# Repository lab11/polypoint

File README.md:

PolyPoint
=========

PolyPoint is a system for using ultra-wideband RF time-of-flight ranging to perform indoor localization.
It incorporates the DecaWave DW1000 for UWB packet transmission and timestamping
into a solder-on module that provides node-to-node ranges over an I2C interface.

Name
----

The name PolyPoint comes from the use of many polygons and shapes in the prototype design and the
desire to pinpoint where users are with the system.

Git Clone
---------

When cloning this repository, be absolutely sure to do

    git clone --recursive https://github.com/lab11/polypoint.git
    
so that you get the submodules as well. All of the supporting
libraries and build tools are in submodules for the various
hardware platforms used in this project.

Hardware
--------

The PolyPoint system is composed of several hardware pieces. At the core is the
TriPoint module which is a 1.25" on a side triangle that encompasses all of the
core ranging hardware and software. TriPoint has castellated edges and can be
soldered on to a carrier board, effectively as a ranging IC. TriTag is one such
carrier board designed to be the tag in the ranging system. It includes the
UWB antennas and a Bluetooth Low Energy radio plus a battery charging circuit.
TriTag is able to provide ranges to a mobile phone application.

### TriPoint

TriPoint includes the following components:

- DecaWave DW1000 UWB radio
- STM32F031G6U6 MCU
- RF switch

The MCU contains all the necessary code to run the DW1000 and the ranging
protocol.

### TriTag

TriTag includes:

- The TriPoint module
- 3 UWB antennas
- nRF51822 BLE radio
- 3.3 V LDO
- Li-ion battery charger

TriTag is designed to be the tag to be localized in the system and connected
to a smartphone.

### TriDev

TriDev is a breakout and testing board for the TriPoint module.
It contains the same BLE hardware as TriTag, but also adds an FTDI
chip for issuing I2C commands over USB.

Software
--------

PolyPoint contains many software layers that run at various levels of
the system.

#### TriPoint

The core firmware that makes the drop-in TriPoint module work
includes all of the logic to implement two way ToF ranging
on top of the DecaWave DW1000 UWB radio. The firmware architecture
supports multiple "applications", or ranging algorithms, that can
be selected at runtime.

#### TriTag

The TriTag code implements a BLE application
that uses the TriPoint module as an I2C device and prov
a BLE service. It puts the TriTag hardware into TAG mode
and provides ranges over a BLE characteristic. 

#### Phone and BLE

The tools in the `/phone` directory interact with TriTag and read data
across the BLE interface.

----

## Academic Publications

The PolyPoint project has led to two academic publications, and an invited talk at HotWireless'16.
If you are interested in the theory behind the ranging protocol, please check out our publications:

 - **[SurePoint: Exploiting Ultra Wideband Flooding and Diversity to Provide Robust, Scalable, High-Fidelity Indoor Localization.](http://lab11.eecs.berkeley.edu/content/pubs/kempke16surepoint.pdf)** Benjamin Kempke, Pat Pannuto, Bradford Campbell, and Prabal Dutta. Proceedings of the 14th ACM Conference on Embedded Networked Sensor Systems (SenSys’16).
 - **[PolyPoint: Guiding Indoor Quadrotors with Ultra-Wideband Localization.](http://lab11.eecs.berkeley.edu/content/pubs/kempke15polypoint.pdf)** Benjamin Kempke, Pat Pannuto, and Prabal Dutta. 2015 ACM Workshop on Hot Topics in Wireless (HotWireless’15).
 
If you use PolyPoint or its derivatives, please use the following citation:

```bibtex
@inproceedings{kempke16surepoint,
	title = {{SurePoint}: Exploiting Ultra Wideband Flooding and Diversity to Provide Robust, Scalable, High-Fidelity Indoor Localization},
	booktitle = {Proceedings of the 14th ACM Conference on Embedded Networked Sensor Systems},
	series = {SenSys'16},
	year = {2016},
	month = {11},
	location = {Stanford, CA, USA},
	conference-url = {http://sensys.acm.org/2016/},
	author = {Kempke, Benjamin and Pannuto, Pat and Campbell, Bradford and Dutta, Prabal},
}
```

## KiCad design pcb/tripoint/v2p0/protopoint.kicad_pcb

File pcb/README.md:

PolyPoint Hardware
==================

The PolyPoint system consists of several PCBs centered around TriPoint,
the core UWB ranging module.

1. **TriPoint**: Triangular module which contains all necessary hardware
for using the DecaWave DW1000. It has castellated headers so it can be
soldered onto a carrier board to add indoor localization functionality
to any device.

2. **TriTag**: Portable carrier board designed to be used as an indoor
localization tag. Has TriPoint on one side and a BLE radio on the other.

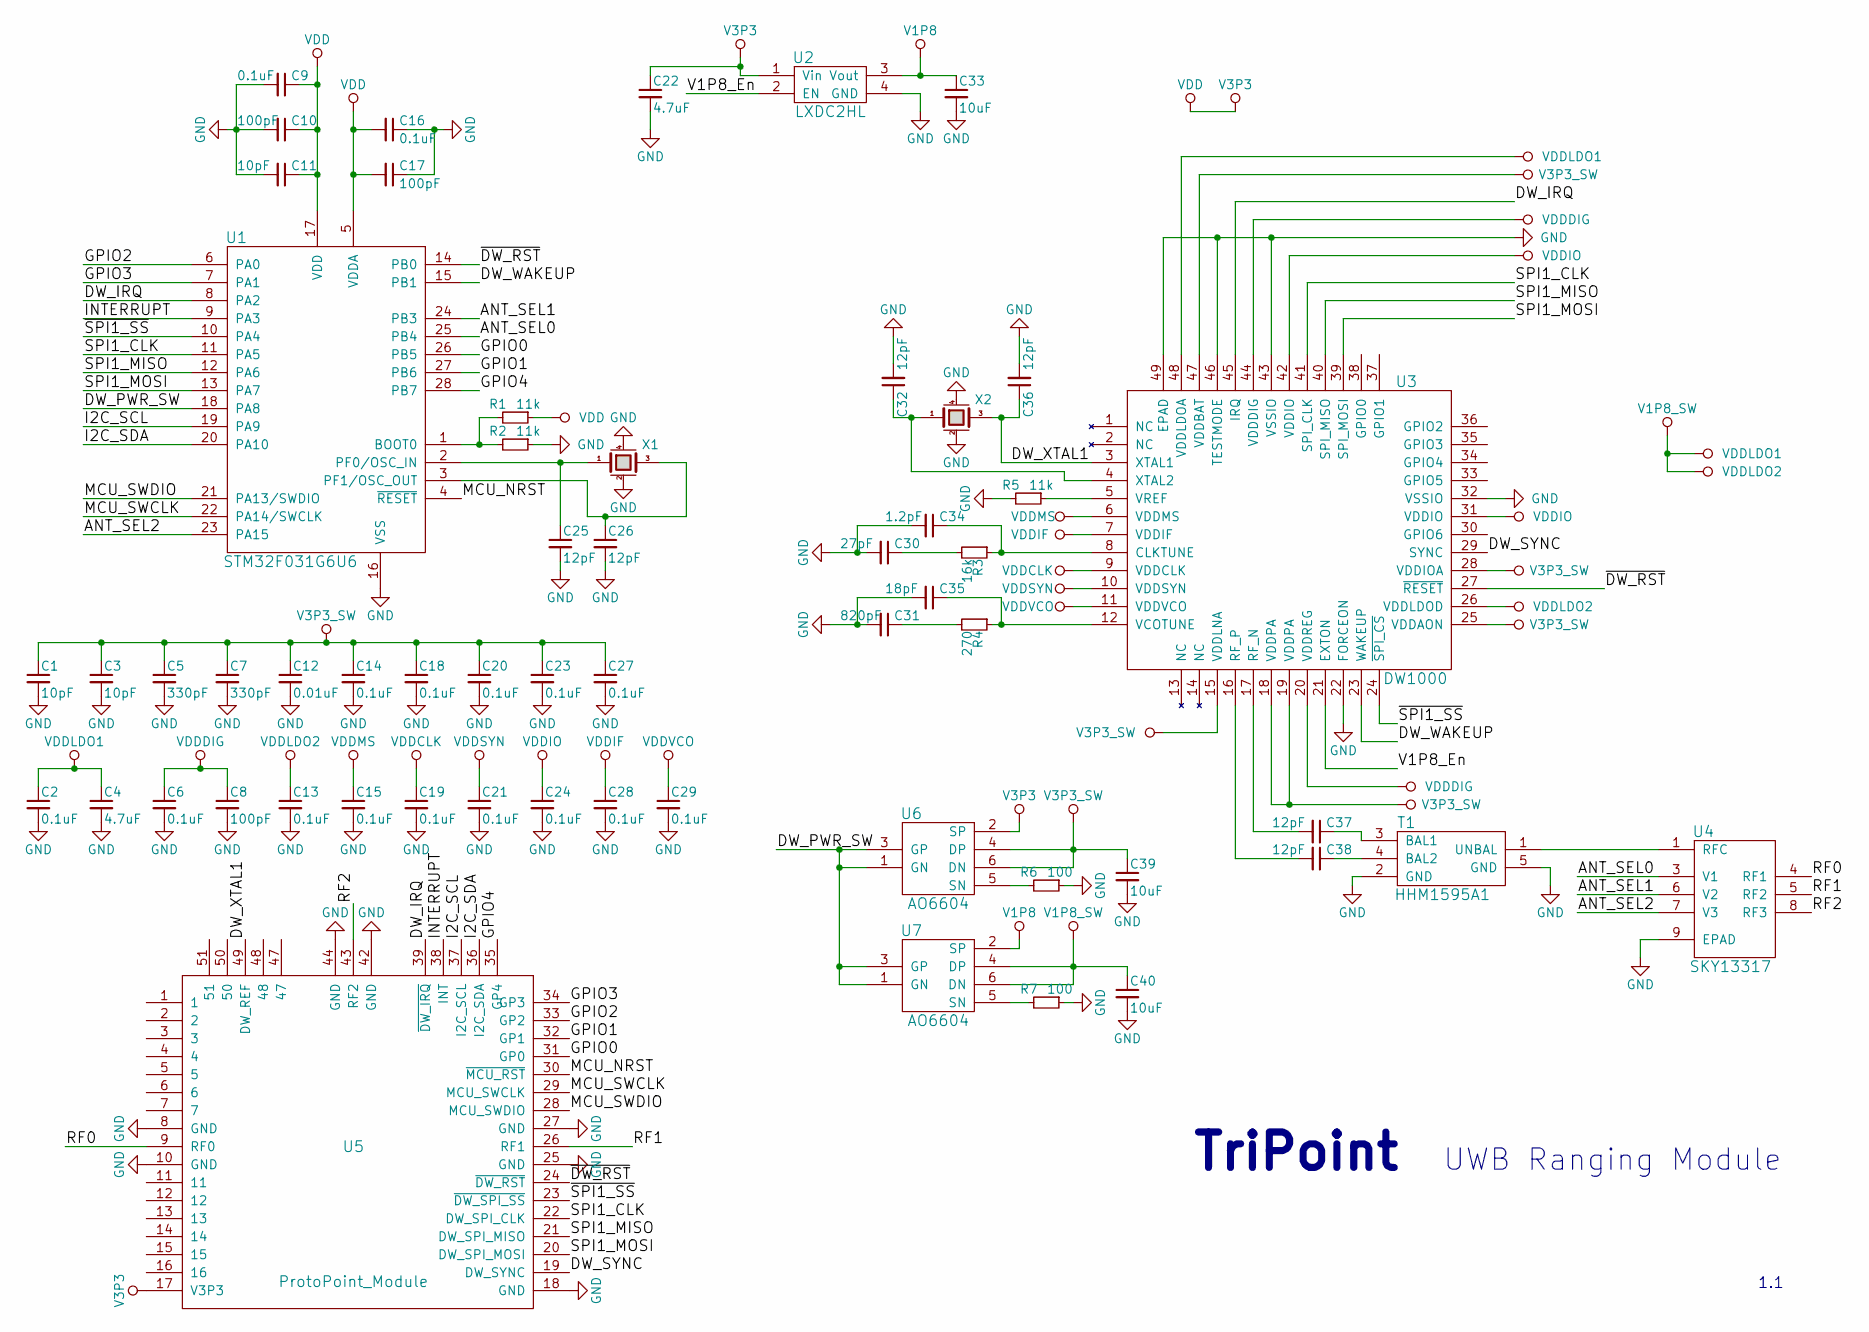
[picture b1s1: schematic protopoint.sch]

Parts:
C1, C3, C11: 10pF; C_0201; ManPartNo GRM0335C1E100JA01D
C2, C6, C9, C13, C14, C15, C16, C18, C19, C20, C21, C23, C24, C27, C28, C29: 0.1uF; C_0201; ManPartNo GRM033R61A104KE15D
C4, C22: 4.7uF; C_0603; ManPartNo GRM188F51A475ZE20D
C5, C7: 330pF; C_0201; ManPartNo GRM033R71E331KA01D
C8, C10, C17: 100pF; C_0201; ManPartNo GRM0335C1E101JA01D
C12: 0.01uF; C_0201; ManPartNo GRM033R71A103KA01D
C25, C26, C32, C36: 12pF; C_0201; ManPartNo GRM0335C1E120JA01D
C30: 27pF; C_0201; ManPartNo GRM0335C1E270JA01D
C31: 820pF; C_0201; ManPartNo GRM033R71E821KA01D
C33, C39, C40: 10uF; C_0603; ManPartNo GRM188R61C106MA73D
C34: 1.2pF; C_0201; ManPartNo GRM0335C1H1R2CA01D
C35: 18pF; C_0201; ManPartNo GRM0335C1H180JA01D
C37, C38: 12pF; C_0402; ManPartNo GRM1555C1H120JA01D
R1, R2, R5: 11k; R_0201; ManPartNo ERJ-1GEF1102C
R3: 16k; R_0201; ManPartNo ERJ-1GEF1602C
R4: 270; R_0201; ManPartNo ERJ-1GEF2700C
R6, R7: 100; R_0201; ManPartNo ERJ-1GEF1102C
T1: HHM1595A1; ManPartNo HHM1595A1
U1: STM32F031G6U6; UFQFPN-28; ManPartNo STM32F031G6U6
U2: LXDC2HL; ManPartNo LXDC2HL18A-052
U3: DW1000; QFN-48-EP-6x6mm; ManPartNo DW1000-I-TR13
U4: SKY13317; MLPQ-UT-8-1.5X1.5mm; ManPartNo SKY13317-373LF
U5: ProtoPoint_Module; ProtoPoint_Module_Castellated
U6, U7: AO6604; TSOP-6
X1: 38.4M; FA-128; ManPartNo FA-20H 38.4000MF10Z-AS3
X2: 16M; FA-128; ManPartNo FA-20H 16.0000MF10Z-AJ3

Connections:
/ANT_SEL0: U1.25 (PB4), U4.3 (V1)
/ANT_SEL1: U1.24 (PB3), U4.6 (V2)
/ANT_SEL2: U1.23 (PA15), U4.7 (V3)
/DW_IRQ: U1.8 (PA2), U3.45 (IRQ), U5.39 (~DW_IRQ)
/DW_PWR_SW: U1.18 (PA8), U6.1 (GN), U6.3 (GP), U7.1 (GN), U7.3 (GP)
/DW_SYNC: U3.29 (SYNC), U5.19 (DW_SYNC)
/DW_WAKEUP: U1.15 (PB1), U3.23 (WAKEUP)
/DW_XTAL1: C36.1, U3.3 (XTAL1), U5.49 (DW_REF), X2.3
/GPIO0: U1.26 (PB5), U5.31 (GP0)
/GPIO1: U1.27 (PB6), U5.32 (GP1)
/GPIO2: U1.6 (PA0), U5.33 (GP2)
/GPIO3: U1.7 (PA1), U5.34 (GP3)
/GPIO4: U1.28 (PB7), U5.35 (GP4)
/I2C_SCL: U1.19 (PA9), U5.37 (I2C_SCL)
/I2C_SDA: U1.20 (PA10), U5.36 (I2C_SDA)
/INTERRUPT: U1.9 (PA3), U5.38 (INT)
/MCU_NRST: U1.4 (~RESET), U5.30 (~MCU_RST)
/MCU_SWCLK: U1.22 (PA14/SWCLK), U5.29 (MCU_SWCLK)
/MCU_SWDIO: U1.21 (PA13/SWDIO), U5.28 (MCU_SWDIO)
/RF0: U4.4 (RF1), U5.9 (RF0)
/RF1: U4.5 (RF2), U5.26 (RF1)
/RF2: U4.8 (RF3), U5.43 (RF2)
/SPI1_CLK: U1.11 (PA5), U3.41 (SPI_CLK), U5.22 (DW_SPI_CLK)
/SPI1_MISO: U1.12 (PA6), U3.40 (SPI_MISO), U5.21 (DW_SPI_MISO)
/SPI1_MOSI: U1.13 (PA7), U3.39 (SPI_MOSI), U5.20 (DW_SPI_MOSI)
/V1P8_En: U2.2 (EN), U3.21 (EXTON)
/~DW_RST: U1.14 (PB0), U3.27 (~RESET), U5.24 (~DW_RST)
/~SPI1_SS: U1.10 (PA4), U3.24 (~SPI_CS), U5.23 (~DW_SPI_SS)
GND: C1.2, C2.2, C3.2, C4.2, C5.2, C6.2, C7.2, C8.2, C9.2, C10.2, C11.2, C12.2, C13.2, C14.2, C15.2, C16.1, C17.1, C18.2, C19.2, C20.2, C21.2, C22.2, C23.2, C24.2, C25.2, C26.2, C27.2, C28.2, C29.2, C30.2, C31.2, C32.2, C33.2, C34.2, C35.2, C36.2, C39.2, C40.2, R2.1, R5.2, R6.1, R7.1, T1.2 (GND), T1.5 (GND), U1.16 (VSS), U2.4 (GND), U3.22 (FORCEON), U3.32 (VSSIO), U3.43 (VSSIO), U3.46 (TESTMODE), U3.49 (EPAD), U4.9 (EPAD), U5.8 (GND), U5.10 (GND), U5.18 (GND), U5.25 (GND), U5.27 (GND), U5.42 (GND), U5.44 (GND), X1.2 (case), X1.4, X2.2 (case), X2.4
unnamed: C25.1, U1.2 (PF0/OSC_IN), X1.1
unnamed: C26.1, U1.3 (PF1/OSC_OUT), X1.3
unnamed: C30.1, R3.2
unnamed: C31.1, R4.2
unnamed: C32.1, U3.4 (XTAL2), X2.1
unnamed: C34.1, R3.1, U3.8 (CLKTUNE)
unnamed: C35.1, R4.1, U3.12 (VCOTUNE)
unnamed: C37.1, T1.3 (BAL1)
unnamed: C37.2, U3.17 (RF_N)
unnamed: C38.1, T1.4 (BAL2)
unnamed: C38.2, U3.16 (RF_P)
unnamed: R1.2, R2.2, U1.1 (BOOT0)
unnamed: R5.1, U3.5 (VREF)
unnamed: R6.2, U6.5 (SN)
unnamed: R7.2, U7.5 (SN)
unnamed: T1.1 (UNBAL), U4.1 (RFC)
V1P8: C33.1, U2.3 (Vout), U7.2 (SP)
V1P8_SW: C2.1, C4.1, C13.1, C40.1, U3.26 (VDDLDOD), U3.48 (VDDLDOA), U7.4 (DP), U7.6 (DN)
V3P3: C9.1, C10.1, C11.1, C16.2, C17.2, C22.1, R1.1, U1.5 (VDDA), U1.17 (VDD), U2.1 (Vin), U5.17 (V3P3), U6.2 (SP)
V3P3_SW: C1.1, C3.1, C5.1, C7.1, C12.1, C14.1, C18.1, C20.1, C23.1, C27.1, C39.1, U3.15 (VDDLNA), U3.18 (VDDPA), U3.19 (VDDPA), U3.25 (VDDAON), U3.28 (VDDIOA), U3.47 (VDDBAT), U6.4 (DP), U6.6 (DN)
VDDCLK: C19.1, U3.9 (VDDCLK)
VDDDIG: C6.1, C8.1, U3.20 (VDDREG), U3.44 (VDDDIG)
VDDIF: C28.1, U3.7 (VDDIF)
VDDIO: C24.1, U3.31 (VDDIO), U3.42 (VDDIO)
VDDMS: C15.1, U3.6 (VDDMS)
VDDSYN: C21.1, U3.10 (VDDSYN)
VDDVCO: C29.1, U3.11 (VDDVCO)

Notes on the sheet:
TriPoint
1.1
UWB Ranging Module

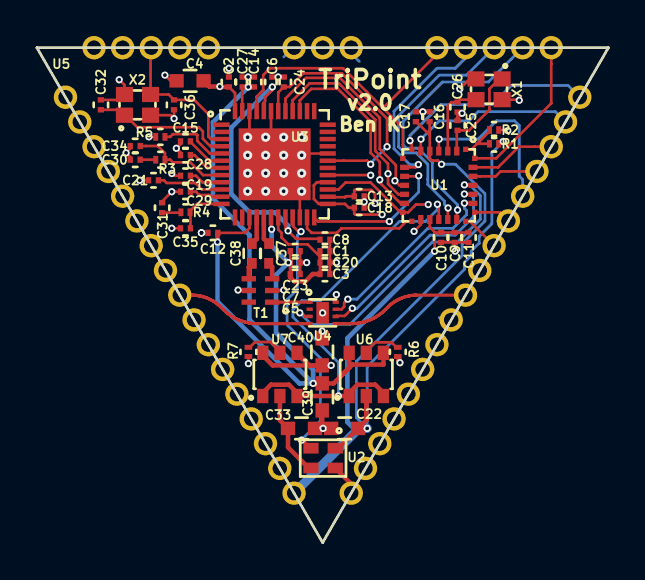
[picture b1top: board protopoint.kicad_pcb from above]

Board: 4 copper layers, 31.8 x 27.5 mm, 57 parts (0 on the bottom side), 56 nets.

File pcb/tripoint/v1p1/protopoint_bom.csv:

Reference, Quantity, Value, Footprint, Datasheet, ManPartNo, DistPartNo
C1 C11 C3 ,3,10pF,Capacitors_SMD:C_0201,,GRM0335C1E100JA01D,490-8607-1-ND
C12 ,1,0.01uF,Capacitors_SMD:C_0201,,GRM033R71A103KA01D,490-3194-1-ND
C13 C14 C15 C16 C18 C19 C2 C20 C21 C23 C24 C27 C28 C29 C6 C9 ,16,0.1uF,Capacitors_SMD:C_0201,,GRM033R61A104KE15D,490-5881-1-ND
C10 C17 C8 ,3,100pF,Capacitors_SMD:C_0201,,GRM0335C1E101JA01D,490-3160-1-ND
C22 C4 ,2,4.7uF,Capacitors_SMD:C_0603,,GRM188F51A475ZE20D,490-3302-1-ND
C25 C26 C32 C36 ,4,12pF,Capacitors_SMD:C_0201,,GRM0335C1E120JA01D,490-3144-1-ND
C30 ,1,27pF,Capacitors_SMD:C_0201,,GRM0335C1E270JA01D,490-3150-1-ND
C31 ,1,820pF,Capacitors_SMD:C_0201,,GRM033R71E821KA01D,490-3183-1-ND
C33 ,1,10uF,Capacitors_SMD:C_0603,,GRM188R61C106MA73D,490-7201-1-ND
C34 ,1,1.2pF,Capacitors_SMD:C_0201,,GRM0335C1H1R2CA01D,490-6119-1-ND
C35 ,1,18pF,Capacitors_SMD:C_0201,,GRM0335C1H180JA01D,490-6117-1-ND
C37 C38 ,2,12pF,Capacitors_SMD:C_0402,,GRM1555C1H120JA01D,490-5924-1-ND
C5 C7 ,2,330pF,Capacitors_SMD:C_0201,,GRM033R71E331KA01D,490-3178-1-ND
R3 ,1,16k,Resistors_SMD:R_0201,,ERJ-1GEF1602C,P16.0KABCT-ND
R4 ,1,270,Resistors_SMD:R_0201,,ERJ-1GEF2700C,P270ABCT-ND
R1 R2 R5 ,3,11k,Resistors_SMD:R_0201,,ERJ-1GEF1102C,P11.0KABCT-ND
T1 ,1,HHM1595A1,polypoint:HHM1595A1,,HHM1595A1,445-3387-1-ND
U1 ,1,STM32F031G6U6,polypoint:UFQFPN-28,,STM32F031G6U6,497-13620-ND
U2 ,1,LXDC2HL,polypoint:LXDC2HL,,LXDC2HL18A-052,490-5791-1-ND
U3 ,1,DW1000,polypoint:QFN-48-EP-6x6mm,,DW1000-I-TR13,1479-1001-1-ND
U4 ,1,SKY13317,polypoint:MLPQ-UT-8-1.5X1.5mm,,SKY13317-373LF,863-1056-1-ND
U5 ,1,ProtoPoint_Module,polypoint:ProtoPoint_Module_Castellated,
X1 ,1,38.4M,polypoint:FA-128,,FA-20H 38.4000MF10Z-AS3,SER3631CT-ND
X2 ,1,16M,polypoint:FA-128,,FA-20H 16.0000MF10Z-AJ3,SER3913CT-ND

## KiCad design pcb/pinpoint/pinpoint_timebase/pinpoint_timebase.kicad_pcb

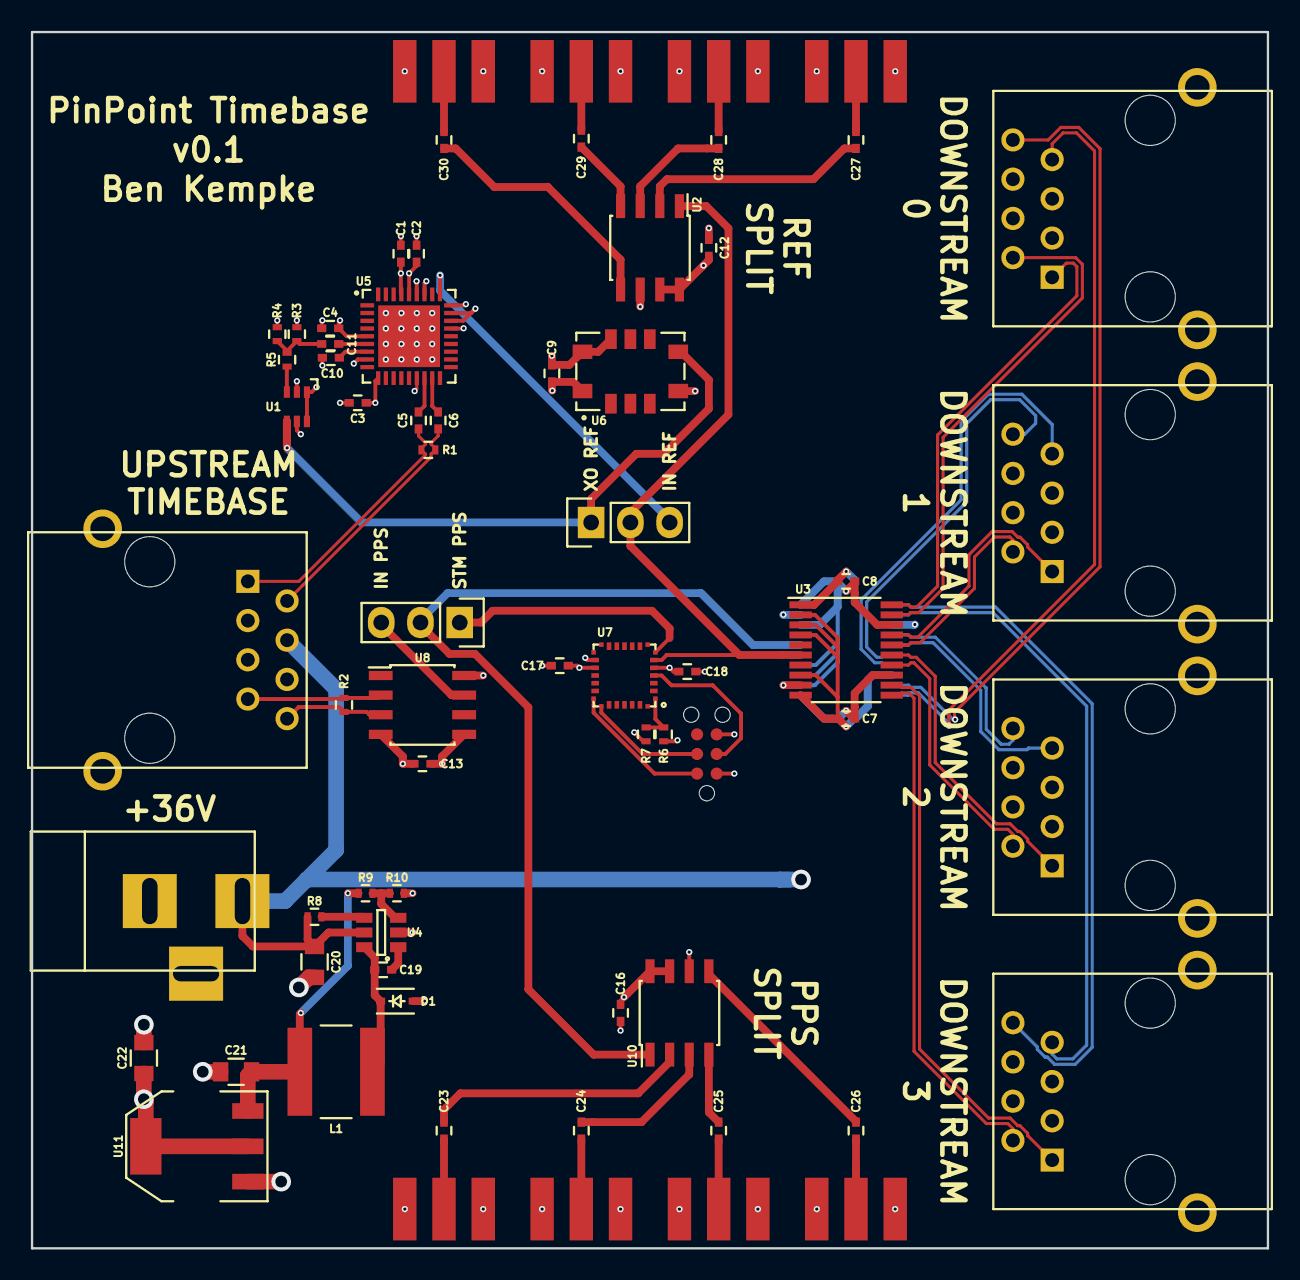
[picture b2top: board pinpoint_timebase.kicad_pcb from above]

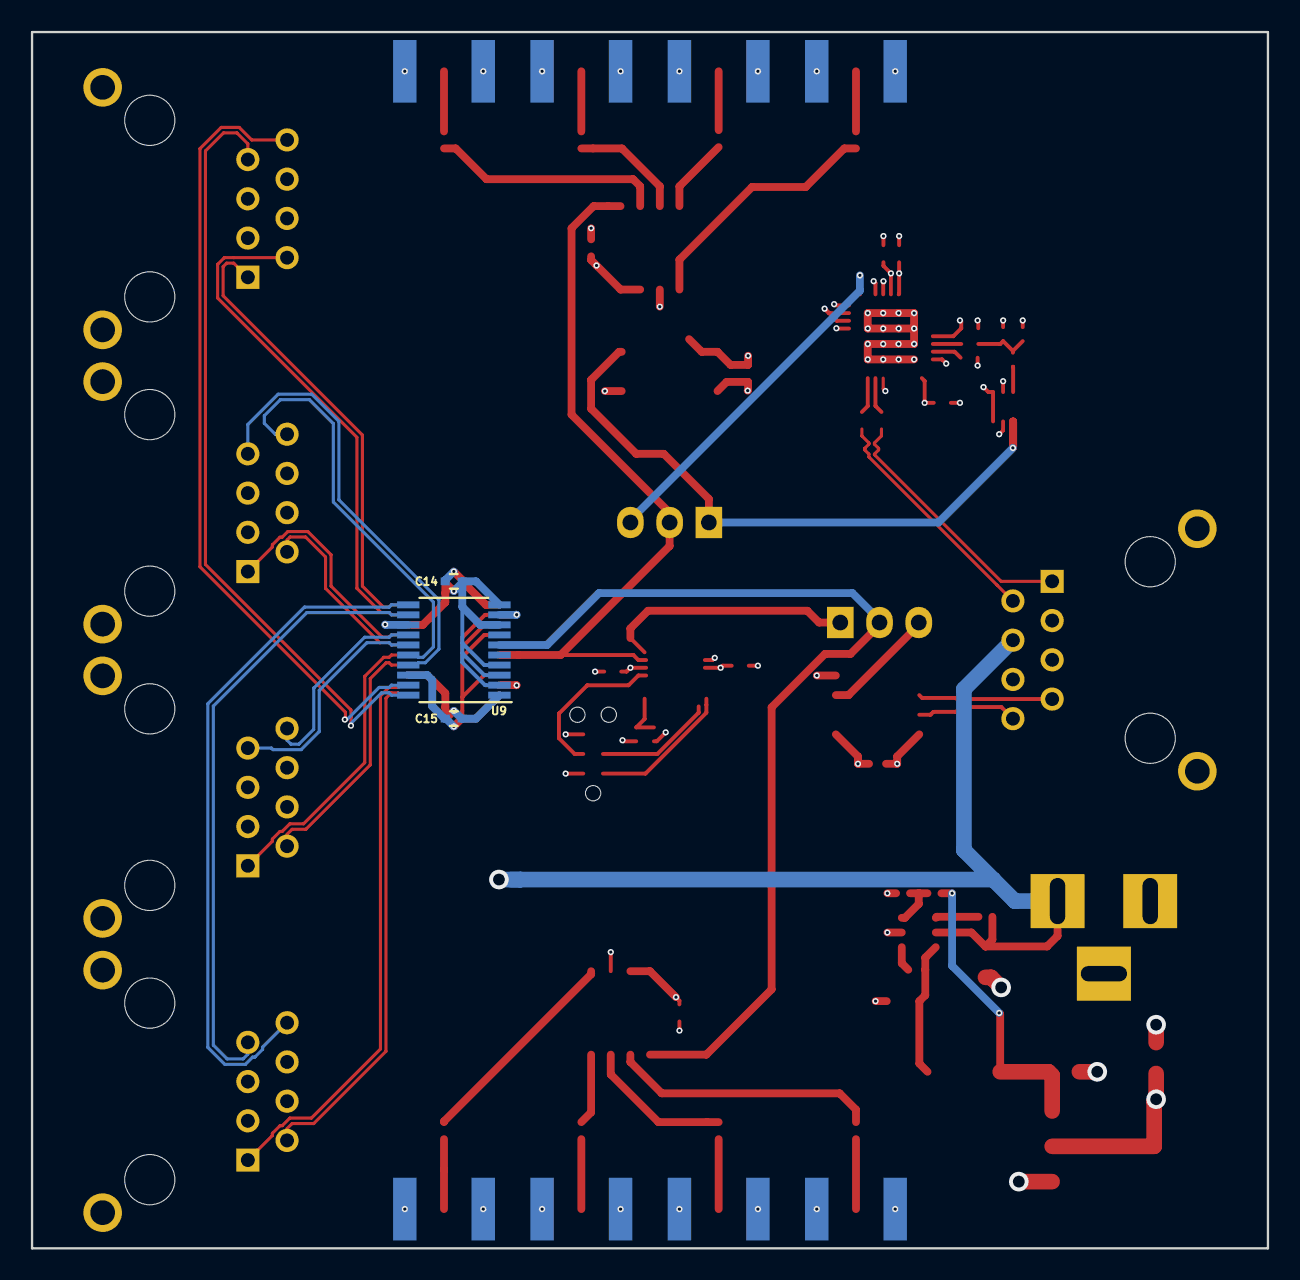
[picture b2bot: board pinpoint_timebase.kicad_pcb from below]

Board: 4 copper layers, 80.0 x 78.7 mm, 70 parts (3 on the bottom side), 60 nets.

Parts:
C1, C2, C3, C4, C5, C6, C7, C8, C9, C10, C11, C12, C13, C14, C15, C16, C17, C18, C19, C23, C24, C25, C26, C27, C28, C29, C30: 0.1uF; C_0402
C20: 4.7uF; C_0805
C21, C22: 10uF; C_0805
CON1: BARREL_JACK
D1: D_Schottky; SOD-323
J1, J2, J3, J4, J5: RJ45; RJ45_8
J6: TC2030-JLINK-NL; TC2030
L1: 22uH; NR6045
P1, P6: CONN_01X03; Pin_Header_Straight_1x03
P2, P3, P4, P5, P8, P9, P10: SMA; SMA_EDGE
R1, R2, R6, R7: R_Small; R_0402
R3, R4: 150; R_0402
R5: 130; R_0402
R8: 4.7K; R_0402
R9: 49.9K; R_0402
R10: 9.53K; R_0402
U1: SN74AVC1T45; SC-70-6
U2, U10: 551S; SOIC-8_3.9x4.9mm_Pitch1.27mm
U3, U9: ICS8545; TSSOP-20_4.4x6.5mm_Pitch0.65mm
U4: AOZ1282CI; SOT-23-6
U5: SI5317; QFN-36_1EP_6x6mm
U6: 7N-XX.XXXMBP-T; 7N-xx.xxxMBP-T
U7: STM32F031G4U6; UFQFPN-28
U8: 830S21; SOIC-8_3.9x4.9mm_Pitch1.27mm
U11: NCP1117; SOT-223
eP7: SMA; SMA_EDGE

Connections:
/CLK0+: J3.1, U3.20
/CLK0-: J3.2, U3.19
/CLK1+: J4.1, U3.17
/CLK1-: J4.2, U3.16
/CLK2+: J1.1, U3.15
/CLK2-: J1.2, U3.14
/CLK3+: J5.1, U3.12
/CLK3-: J5.2, U3.11
/IN_PPS+: J2.7, R2.1, U8.2
/IN_PPS-: J2.8, R2.2, U8.3
/IN_REF+: C5.2, J2.1, R1.1
/IN_REF-: C6.2, J2.2, R1.2
/PPS0+: J3.7, U9.20
/PPS0-: J3.8, U9.19
/PPS1+: J4.7, U9.17
/PPS1-: J4.8, U9.16
/PPS2+: J1.7, U9.15
/PPS2-: J1.8, U9.14
/PPS3+: J5.7, U9.12
/PPS3-: J5.8, U9.11
/REFTMP+: C5.1, U5.16
/REFTMP-: C6.1, U5.17
/SYS_CLK: P1.2, U2.1, U3.6, U7.6
GND: C1.2, C2.1, C3.2, C4.1, C7.2, C8.1, C9.2, C10.1, C12.2, C13.2, C14.2, C15.1, C16.2, C17.2, C18.1, C20.2, C21.2, C22.2, CON1.2, CON1.3, D1.2, J1.5, J1.9, J2.5, J2.9, J3.5, J3.9, J4.5, J4.9, J5.5, J5.9, J6.5, P2.2, P3.2, P4.2, P5.2, P8.2, P9.2, P10.2, R4.1, R7.2, R10.2, U1.2, U1.5, U2.6, U3.1, U3.9, U3.13, U4.2, U5.8, U5.15, U5.24, U5.27, U5.30, U5.31, U5.37, U6.4, U6.10, U7.16, U8.5, U9.1, U9.9, U9.13, U10.6, U11.1, eP7.2
unnamed: C10.2, U5.7
unnamed: C11.1, R3.1, R4.2, R5.2
unnamed: C11.2, U5.6
unnamed: C19.1, D1.1, L1.1, U4.6
unnamed: C19.2, U4.1
unnamed: C21.1, L1.2, R9.1, U11.3
unnamed: C23.1, U10.2
unnamed: C23.2, eP7.1
unnamed: C24.1, U10.3
unnamed: C24.2, P8.1
unnamed: C25.1, U10.4
unnamed: C25.2, P9.1
unnamed: C26.1, U10.5
unnamed: C26.2, P10.1
unnamed: C27.1, U2.2
unnamed: C27.2, P2.1
unnamed: C28.1, U2.3
unnamed: C28.2, P3.1
unnamed: C29.1, U2.4
unnamed: C29.2, P4.1
unnamed: C30.1, U2.5
unnamed: C30.2, P5.1
unnamed: J6.2, U7.21
unnamed: J6.3, U7.4
unnamed: J6.4, U7.22
unnamed: P1.1, U1.4, U6.5
unnamed: P1.3, U5.28
unnamed: P6.1, U7.7
unnamed: P6.2, U9.6, U10.1
unnamed: P6.3, U8.7
unnamed: R5.1, U1.3
unnamed: R6.1, R7.1, U7.1
unnamed: R8.2, U4.4
unnamed: R9.2, R10.1, U4.3
V3P3: C1.1, C2.2, C3.1, C4.2, C7.1, C8.2, C9.1, C12.1, C13.1, C14.1, C15.2, C16.1, C17.1, C18.2, C22.1, J6.1, R3.2, R6.2, U1.1, U1.6, U2.7, U2.8, U3.2, U3.3, U3.4, U3.8, U3.10, U3.18, U5.5, U5.10, U5.25, U5.26, U5.32, U5.33, U6.8, U6.9, U7.5, U7.17, U8.4, U8.8, U9.2, U9.3, U9.4, U9.8, U9.10, U9.18, U10.7, U10.8, U11.2, U11.4
VDD: C20.1, CON1.1, J1.4, J2.4, J3.4, J4.4, J5.4, R8.1, U4.5

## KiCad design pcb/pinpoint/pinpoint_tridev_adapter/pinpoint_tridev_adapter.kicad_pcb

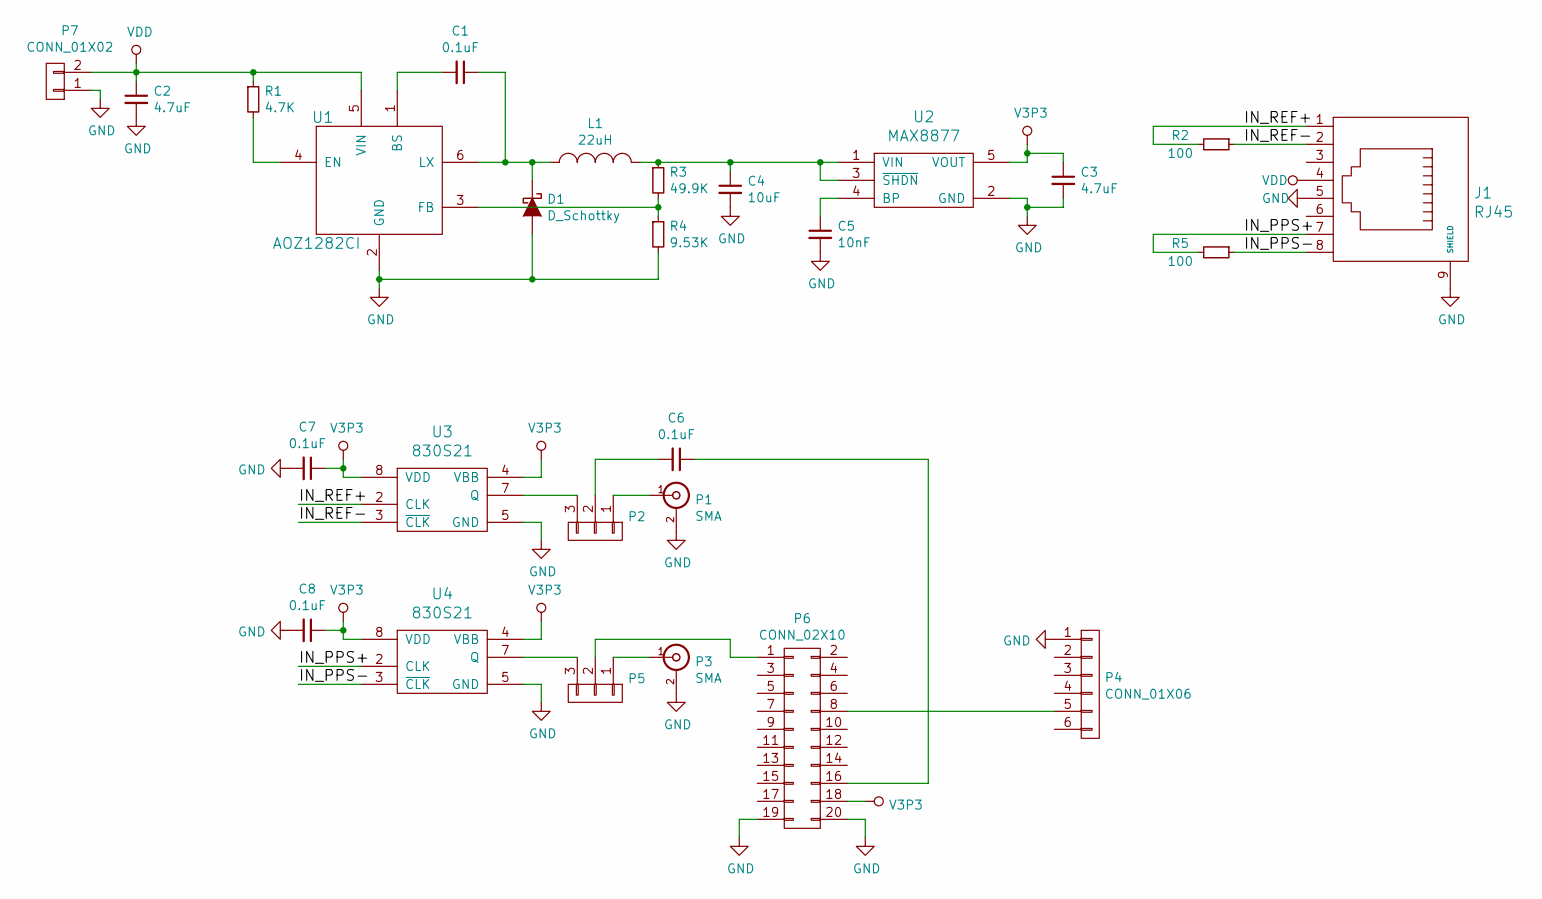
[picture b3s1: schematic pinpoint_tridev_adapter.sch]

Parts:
C1, C6, C7, C8: 0.1uF; C_0402; ManPartNo GRM155R62A104KE14D
C2, C3: 4.7uF; C_0805; ManPartNo GRM21BR61H475KE51L
C4: 10uF; C_0805; ManPartNo GRM21BR61C106KE15K
C5: 10nF; C_0402; ManPartNo GRM155R71H103KA88D
D1: D_Schottky; SOD-323
J1: RJ45; RJ45_8; ManPartNo A-2004-2-4-LPS-N-R
L1: 22uH; NR6045; ManPartNo NR6045T220M
P1, P3: SMA; SMA_EDGE; ManPartNo CONSMA003.062
P2, P5: CONN_01X03; Pin_Header_Straight_1x03
P4: CONN_01X06; Pin_Header_Straight_1x06
P6: CONN_02X10; Pin_Header_Straight_2x10; ManPartNo SSQ-110-03-T-D
P7: CONN_01X02; Pin_Header_Straight_1x02
R1: 4.7K; R_0402; ManPartNo ERJ-2RKF4701X
R2, R5: 100; R_0402; ManPartNo ERJ-2RKF1000X
R3: 49.9K; R_0402; ManPartNo ERJ-2RKF4992X
R4: 9.53K; R_0402; ManPartNo ERJ-2RKF9531X
U1: AOZ1282CI; SOT-23-6; ManPartNo AOZ1282CI
U2: MAX8877; SOT-23-5; ManPartNo MAX8877EUK33+T
U3, U4: 830S21; SOIC-8_3.9x4.9mm_Pitch1.27mm; ManPartNo 830S21AMI-01LF

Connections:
/IN_PPS+: J1.7, R5.2, U4.2 (CLK)
/IN_PPS-: J1.8, R5.1, U4.3 (~CLK)
/IN_REF+: J1.1, R2.2, U3.2 (CLK)
/IN_REF-: J1.2, R2.1, U3.3 (~CLK)
GND: C2.2, C3.2, C4.2, C5.2, C7.2, C8.2, D1.2 (A), J1.5, J1.9 (SHIELD), P1.2 (Ext), P3.2 (Ext), P4.1, P6.19, P6.20, P7.1, R4.2, U1.2 (GND), U2.2 (GND), U3.5 (GND), U4.5 (GND)
unnamed: C1.1, D1.1 (K), L1.1, U1.6 (LX)
unnamed: C1.2, U1.1 (BS)
unnamed: C4.1, L1.2, R3.1, U2.1 (VIN), U2.3 (~SHDN)
unnamed: C5.1, U2.4 (BP)
unnamed: C6.1, P6.16
unnamed: C6.2, P2.2
unnamed: P1.1 (In), P2.1
unnamed: P2.3, U3.7 (Q)
unnamed: P3.1 (In), P5.1
unnamed: P4.5, P6.8
unnamed: P5.2, P6.1
unnamed: P5.3, U4.7 (Q)
unnamed: R1.2, U1.4 (EN)
unnamed: R3.2, R4.1, U1.3 (FB)
V3P3: C3.1, C7.1, C8.1, P6.18, U2.5 (VOUT), U3.4 (VBB), U3.8 (VDD), U4.4 (VBB), U4.8 (VDD)
VDD: C2.1, J1.4, P7.2, R1.1, U1.5 (VIN)

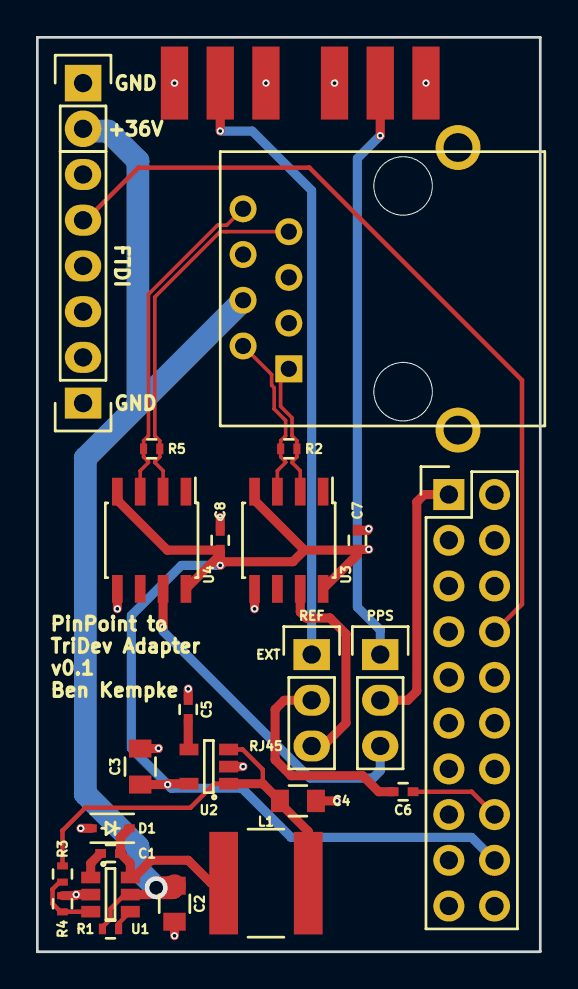
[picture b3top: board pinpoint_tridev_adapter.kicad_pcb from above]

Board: 2 copper layers, 27.9 x 50.8 mm, 27 parts (0 on the bottom side), 21 nets.

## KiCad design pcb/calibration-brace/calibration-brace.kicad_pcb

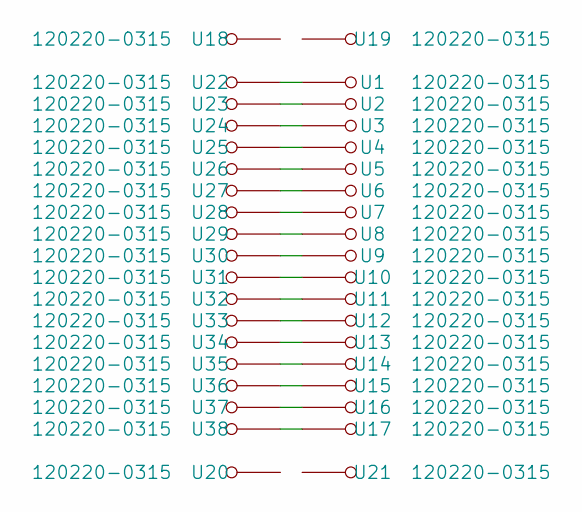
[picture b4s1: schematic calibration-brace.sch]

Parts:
U1, U2, U3, U4, U5, U6, U7, U8, U9, U10, U11, U12, U13, U14, U15, U16, U17, U18, U19, U20, U21, U22, U23, U24, U25, U26, U27, U28, U29, U30, U31, U32, U33, U34, U35, U36, U37, U38: 120220-0315

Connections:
unnamed: U1.1, U22.1
unnamed: U2.1, U23.1
unnamed: U10.1, U31.1
unnamed: U11.1, U32.1
unnamed: U12.1, U33.1
unnamed: U13.1, U34.1
unnamed: U14.1, U35.1
unnamed: U15.1, U36.1
unnamed: U16.1, U37.1
unnamed: U17.1, U38.1
unnamed: U3.1, U24.1
unnamed: U4.1, U25.1
unnamed: U5.1, U26.1
unnamed: U6.1, U27.1
unnamed: U7.1, U28.1
unnamed: U8.1, U29.1
unnamed: U9.1, U30.1

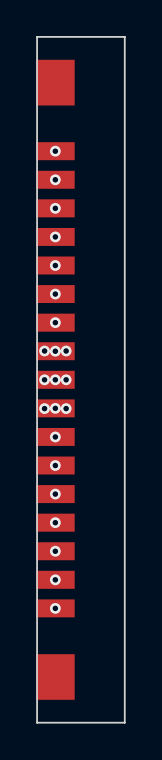
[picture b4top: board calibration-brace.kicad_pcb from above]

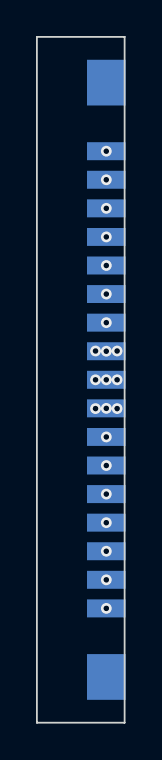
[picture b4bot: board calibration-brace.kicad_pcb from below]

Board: 2 copper layers, 4.9 x 38.1 mm, 38 parts (19 on the bottom side), 17 nets.
